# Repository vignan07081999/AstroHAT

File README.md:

### AstroHAT
## Raspberry Pi HAT for Astrophotography

This project is centered around developing a custom Raspberry Pi HAT designed to enhance astrophotography setups. It aims to streamline power management, integrate essential functionalities, and provide a platform for further expansion.

**Astrophotography**

Astrophotography is a specialized field of photography that captures celestial objects and phenomena. This often involves long exposure times, precise tracking, and specialized equipment.

**Stellarmate OS**

Stellarmate OS is a Linux distribution tailored for astrophotography. It provides a user-friendly interface and integrates with various astronomy software and hardware.

**ASCOM and INDI Protocols**

ASCOM and INDI are communication protocols widely used in astrophotography to facilitate interaction between different devices and software. ASCOM is primarily used on Windows, while INDI is platform-independent.

**Project Overview**

This custom Raspberry Pi HAT is currently under development with the following features and goals:

* **Power Management:**  Provides a centralized power solution for the Raspberry Pi and connected astrophotography devices. 
* **EEPROM:**  Includes an EEPROM for storing configuration data and other persistent information.
* **Real-Time Clock (RTC):**  Features a built-in RTC to ensure accurate timekeeping, even without an internet connection.

**Future Plans**

The project roadmap includes:

* **GPS Integration:**  Adding GPS functionality to enable precise location and time tracking.
* **Reduced Footprint:**  Optimizing the design to minimize the HAT's size and weight.
* **External USB Support:**  Including support for connecting additional USB devices.

**Current Status**

The project is actively in progress. The core functionalities of power management, EEPROM, and RTC are being developed and tested.

**Contributions**

Contributions, suggestions, and feedback are welcome! Please feel free to open issues or submit pull requests. 

**License**

This project is not yet licensed

**Disclaimer**

This project is experimental and may undergo significant changes. Use at your own risk.

**Let's make astrophotography more accessible and enjoyable!**

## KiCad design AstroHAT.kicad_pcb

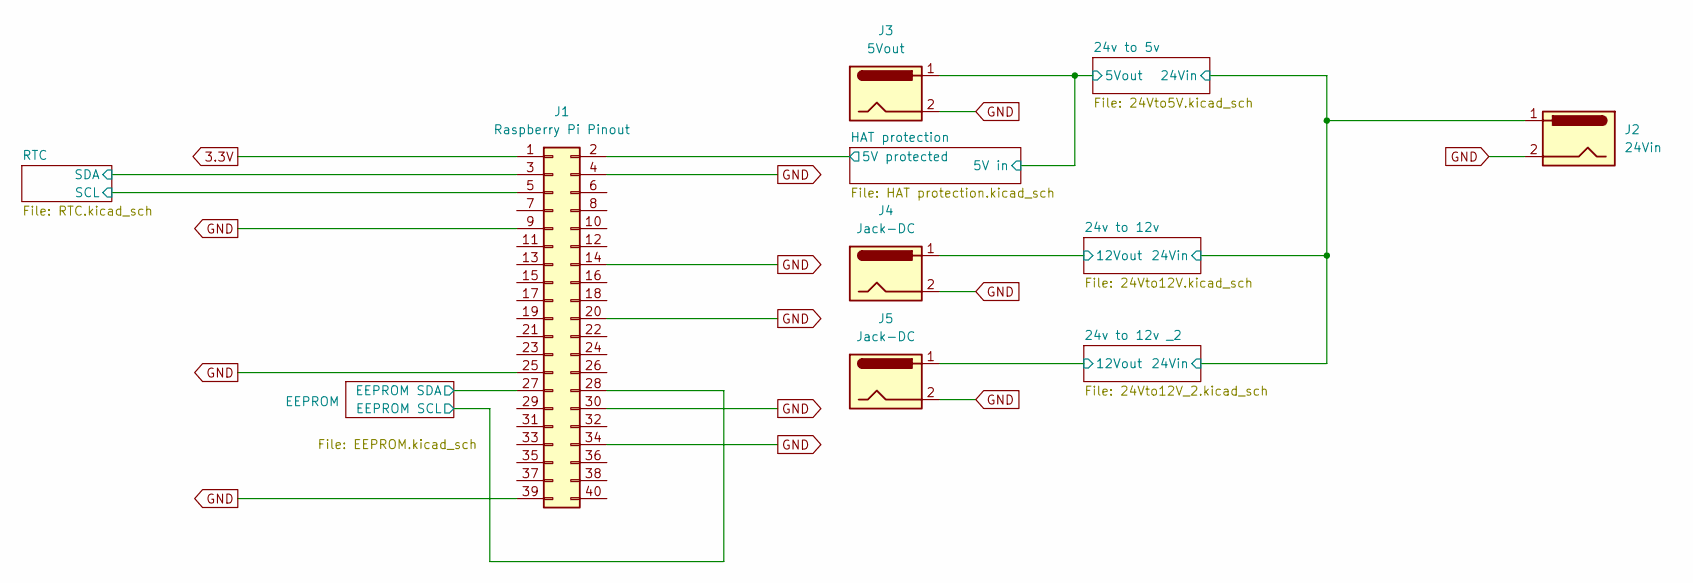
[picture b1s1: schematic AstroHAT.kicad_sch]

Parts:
J1: Raspberry Pi Pinout; PinSocket_2x20_P2.54mm_Vertical
J2: 24Vin; BarrelJack_CUI_PJ-102AH_Horizontal
J3: 5Vout; BarrelJack_CUI_PJ-102AH_Horizontal
J4, J5: Jack-DC; BarrelJack_CUI_PJ-102AH_Horizontal

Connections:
3.3V: J1.1; also elsewhere on the board
/24v to 5v/5Vout: J3.1; also elsewhere on the board
/24v to 12v _2/12Vout: J5.1; also elsewhere on the board
/24v to 12v _2/24Vin: J2.1; also elsewhere on the board
/24v to 12v/12Vout: J4.1; also elsewhere on the board
/EEPROM/EEPROM SCL: J1.28; also elsewhere on the board
/EEPROM/EEPROM SDA: J1.27; also elsewhere on the board
/HAT protection/5V protected: J1.2; also elsewhere on the board
/RTC/SCL: J1.5; also elsewhere on the board
/RTC/SDA: J1.3; also elsewhere on the board
GND: J1.4, J1.9, J1.14, J1.20, J1.25, J1.30, J1.34, J1.39, J2.2, J3.2, J4.2, J5.2; also elsewhere on the board

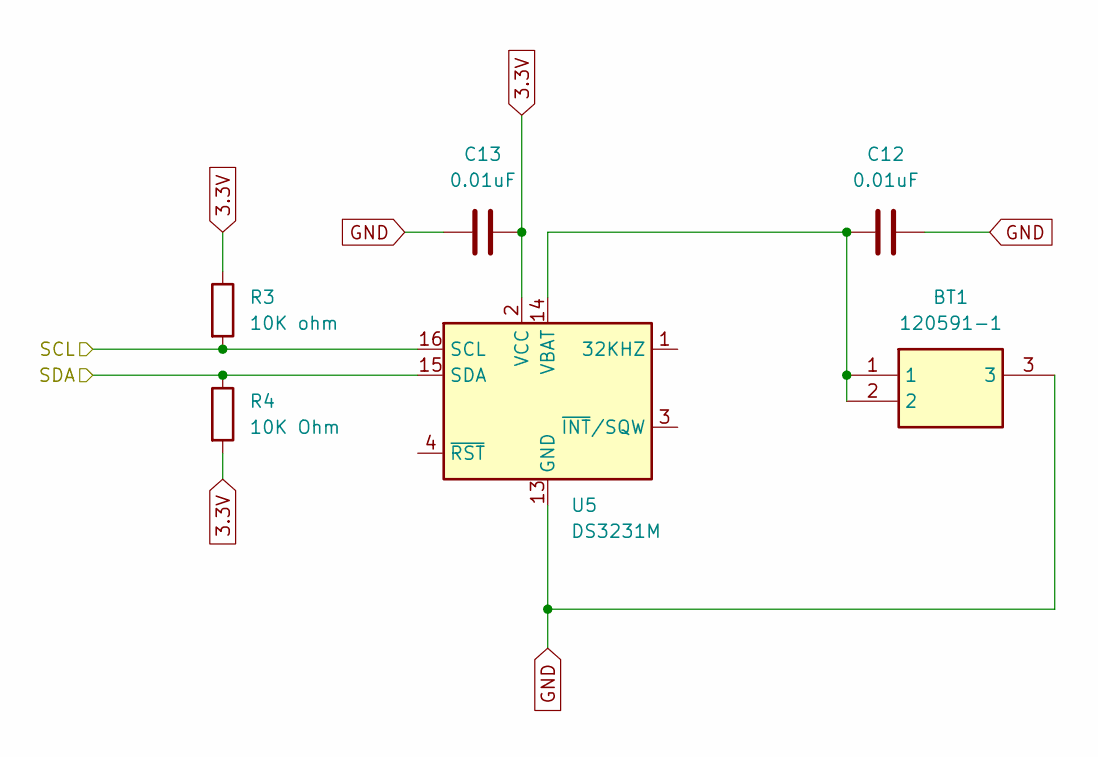
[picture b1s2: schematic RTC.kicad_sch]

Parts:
BT1: 120591-1; Mouser Part Number 571-1205911
C12, C13: 0.01uF; C_0201_0603Metric
R3: 10K ohm; R_2512_6332Metric
R4: 10K Ohm; R_2512_6332Metric
U5: DS3231M; SOIC-16W_7.5x10.3mm_P1.27mm

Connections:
3.3V: C13.2, R3.1, R4.2, U5.2 (VCC); also elsewhere on the board
/RTC/SCL: R3.2, U5.16 (SCL); also elsewhere on the board
/RTC/SDA: R4.1, U5.15 (SDA); also elsewhere on the board
GND: BT1.3, C12.2, C13.1, U5.5 (GND), U5.6 (GND), U5.7 (GND), U5.8 (GND), U5.9 (GND), U5.10 (GND), U5.11 (GND), U5.12 (GND), U5.13 (GND); also elsewhere on the board
unnamed: BT1.1, BT1.2, C12.1, U5.14 (VBAT)

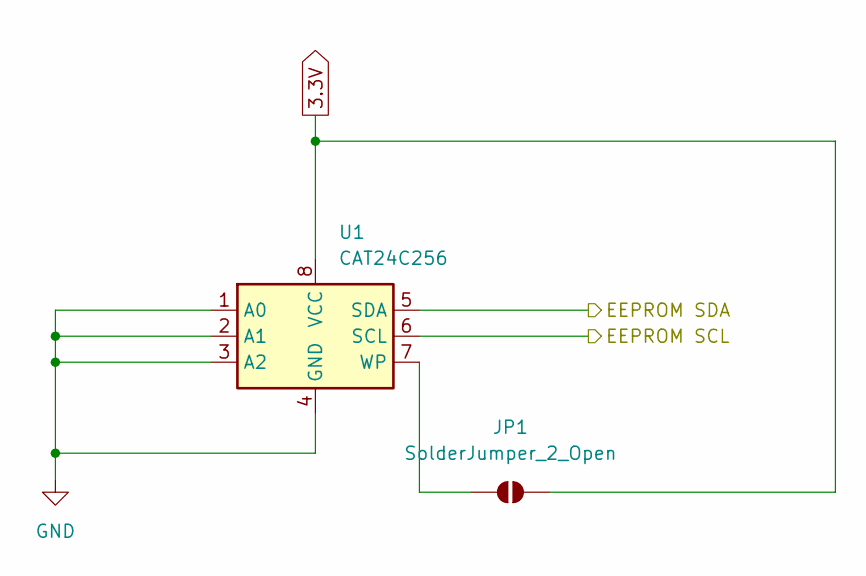
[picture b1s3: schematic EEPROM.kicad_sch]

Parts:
JP1: SolderJumper_2_Open; SolderJumper-2_P1.3mm_Open_RoundedPad1.0x1.5mm
U1: CAT24C256; SOIC127P600X175-8N

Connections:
3.3V: JP1.2 (B), U1.8 (VCC); also elsewhere on the board
/EEPROM/EEPROM SCL: U1.6 (SCL); also elsewhere on the board
/EEPROM/EEPROM SDA: U1.5 (SDA); also elsewhere on the board
GND: U1.1 (A0), U1.2 (A1), U1.3 (A2), U1.4 (GND); also elsewhere on the board
unnamed: JP1.1 (A), U1.7 (WP)

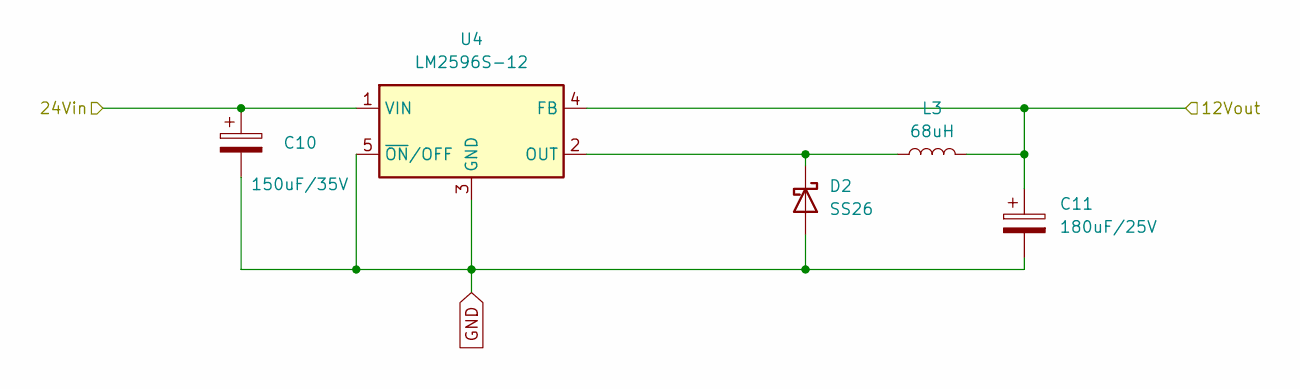
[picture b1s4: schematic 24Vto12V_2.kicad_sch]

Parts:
C10: 150uF/35V; EEHZA1H680P
C11: 180uF/25V; CAPAE830X700N
D2: SS26; D_SMA
L3: 68uH; PA4344683NLT
U4: LM2596S-12; TO-263-5_TabPin3

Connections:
/24v to 12v _2/12Vout: C11.1, L3.2, U4.4 (FB); also elsewhere on the board
/24v to 12v _2/24Vin: C10.1, U4.1 (VIN); also elsewhere on the board
GND: C10.2, C11.2, D2.2 (A), U4.3 (GND), U4.5 (~ON/OFF); also elsewhere on the board
unnamed: D2.1 (K), L3.1, U4.2 (OUT)

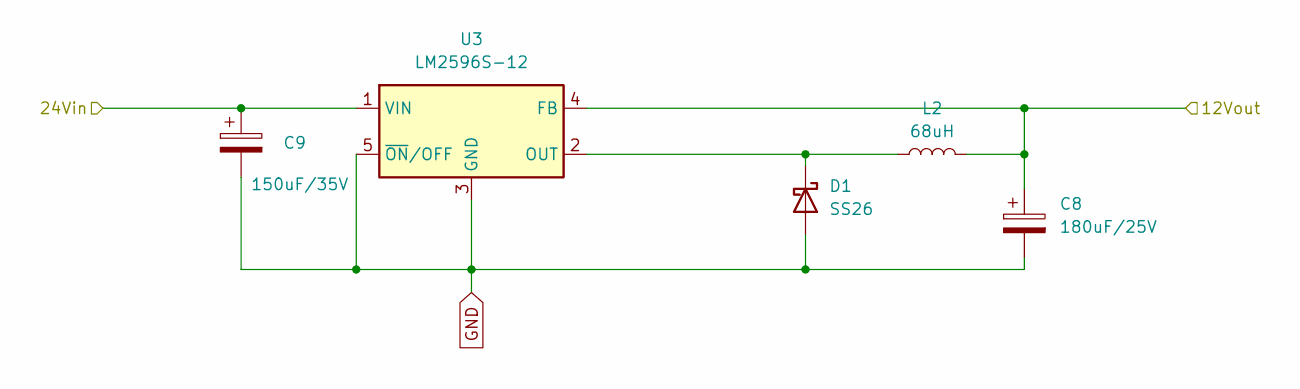
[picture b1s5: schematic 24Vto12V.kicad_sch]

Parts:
C8: 180uF/25V; CAPAE830X700N
C9: 150uF/35V; EEHZA1H680P
D1: SS26; D_SMA
L2: 68uH; PA4344683NLT
U3: LM2596S-12; TO-263-5_TabPin3

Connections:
/24v to 12v _2/24Vin: C9.1, U3.1 (VIN); also elsewhere on the board
/24v to 12v/12Vout: C8.1, L2.2, U3.4 (FB); also elsewhere on the board
GND: C8.2, C9.2, D1.2 (A), U3.3 (GND), U3.5 (~ON/OFF); also elsewhere on the board
unnamed: D1.1 (K), L2.1, U3.2 (OUT)

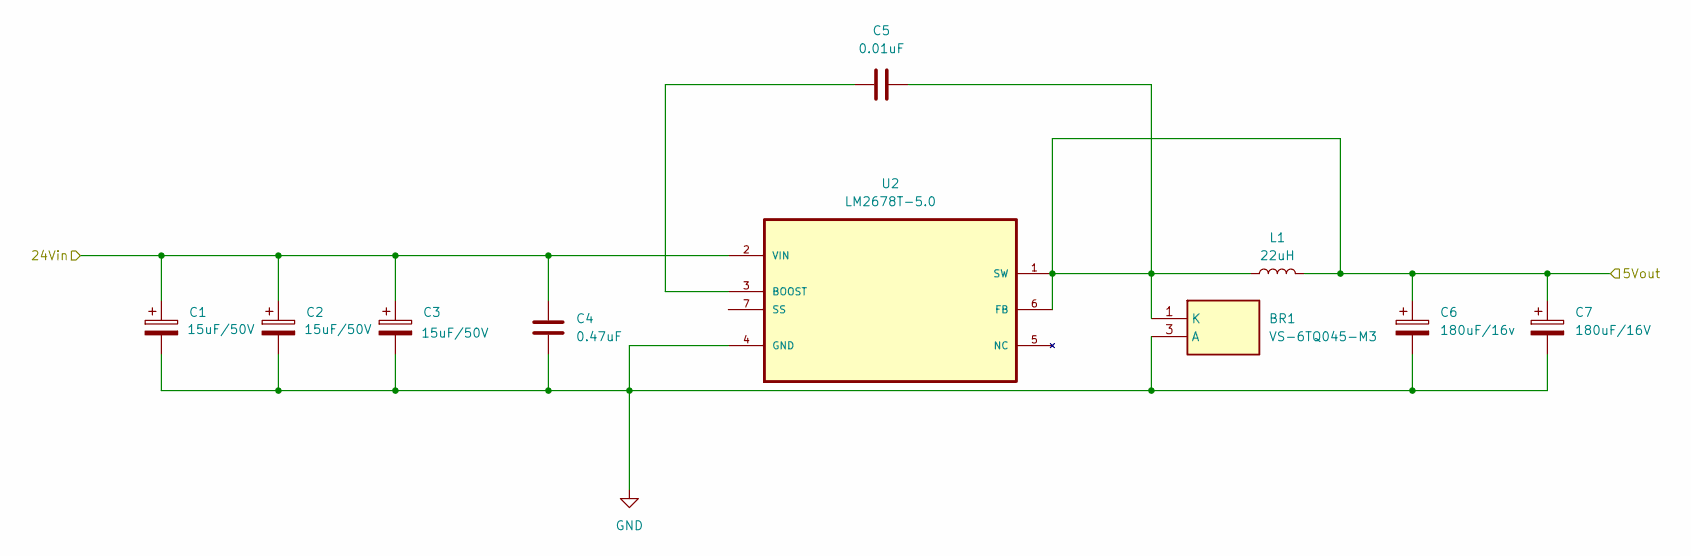
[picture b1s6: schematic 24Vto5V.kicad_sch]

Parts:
BR1: VS-6TQ045-M3; VS6TQ045STRLM3; Mouser Part Number 78-VS-6TQ045-M3
C1, C2, C3: 15uF/50V; CAPAE660X850N
C4: 0.47uF; CAPC3216X152N
C5: 0.01uF; C_0201_0603Metric
C6: 180uF/16v; CAPPC5958X380N
C7: 180uF/16V; CAPPC5958X380N
L1: 22uH; L_Wuerth_MAPI-4020
U2: LM2678T-5.0; TO127P1435X464-8N; MPN LLM2678T-5.0

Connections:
/24v to 5v/5Vout: BR1.1 (K), C5.1, C6.1, C7.1, L1.1, L1.2, U2.1 (SW), U2.6 (FB); also elsewhere on the board
/24v to 12v _2/24Vin: C1.1, C2.1, C3.1, C4.1, U2.2 (VIN); also elsewhere on the board
GND: BR1.3 (A), C1.2, C2.2, C3.2, C4.2, C6.2, C7.2, U2.4 (GND); also elsewhere on the board
unnamed: C5.2, U2.3 (BOOST)

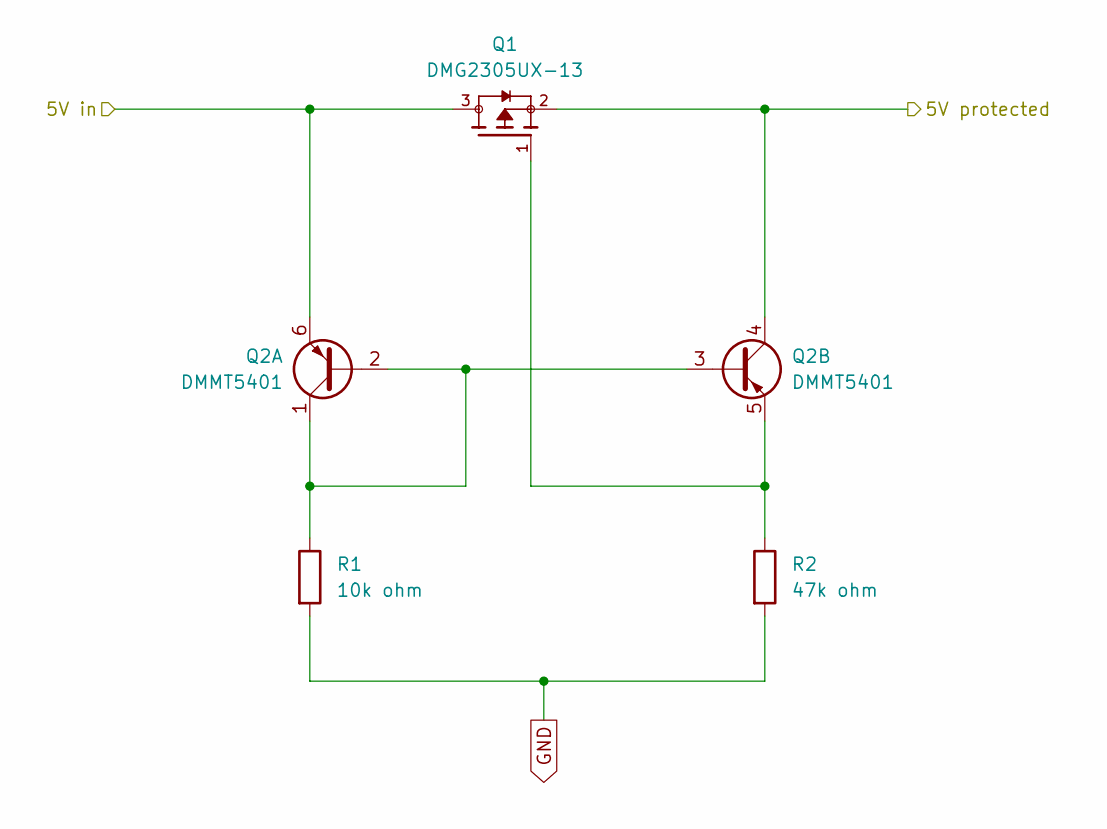
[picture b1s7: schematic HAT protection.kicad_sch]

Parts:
Q1: DMG2305UX-13; SOT91P240X110-3N; PARTREV 09/2018
Q2: DMMT5401; SOT-23-6
R1: 10k ohm; R_0201_0603Metric
R2: 47k ohm; R_0201_0603Metric

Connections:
/24v to 5v/5Vout: Q1.3, Q2.6 (E1); also elsewhere on the board
/HAT protection/5V protected: Q1.2, Q2.4 (C2); also elsewhere on the board
GND: R1.2, R2.2; also elsewhere on the board
unnamed: Q2.1 (C1), Q2.2 (B1), Q2.3 (B2), R1.1
unnamed: Q1.1, Q2.5 (E2), R2.1

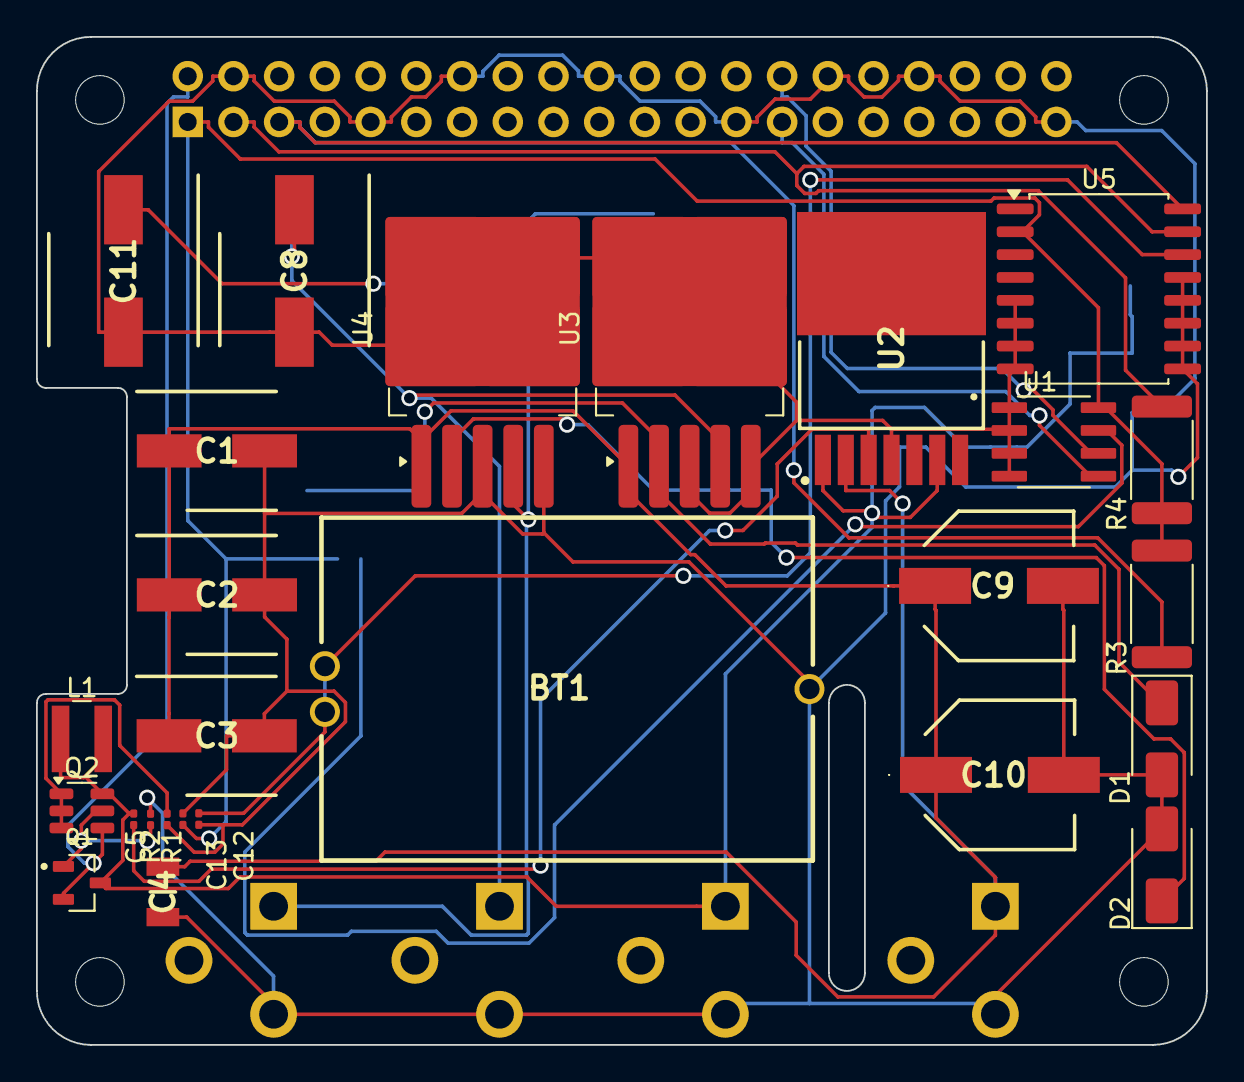
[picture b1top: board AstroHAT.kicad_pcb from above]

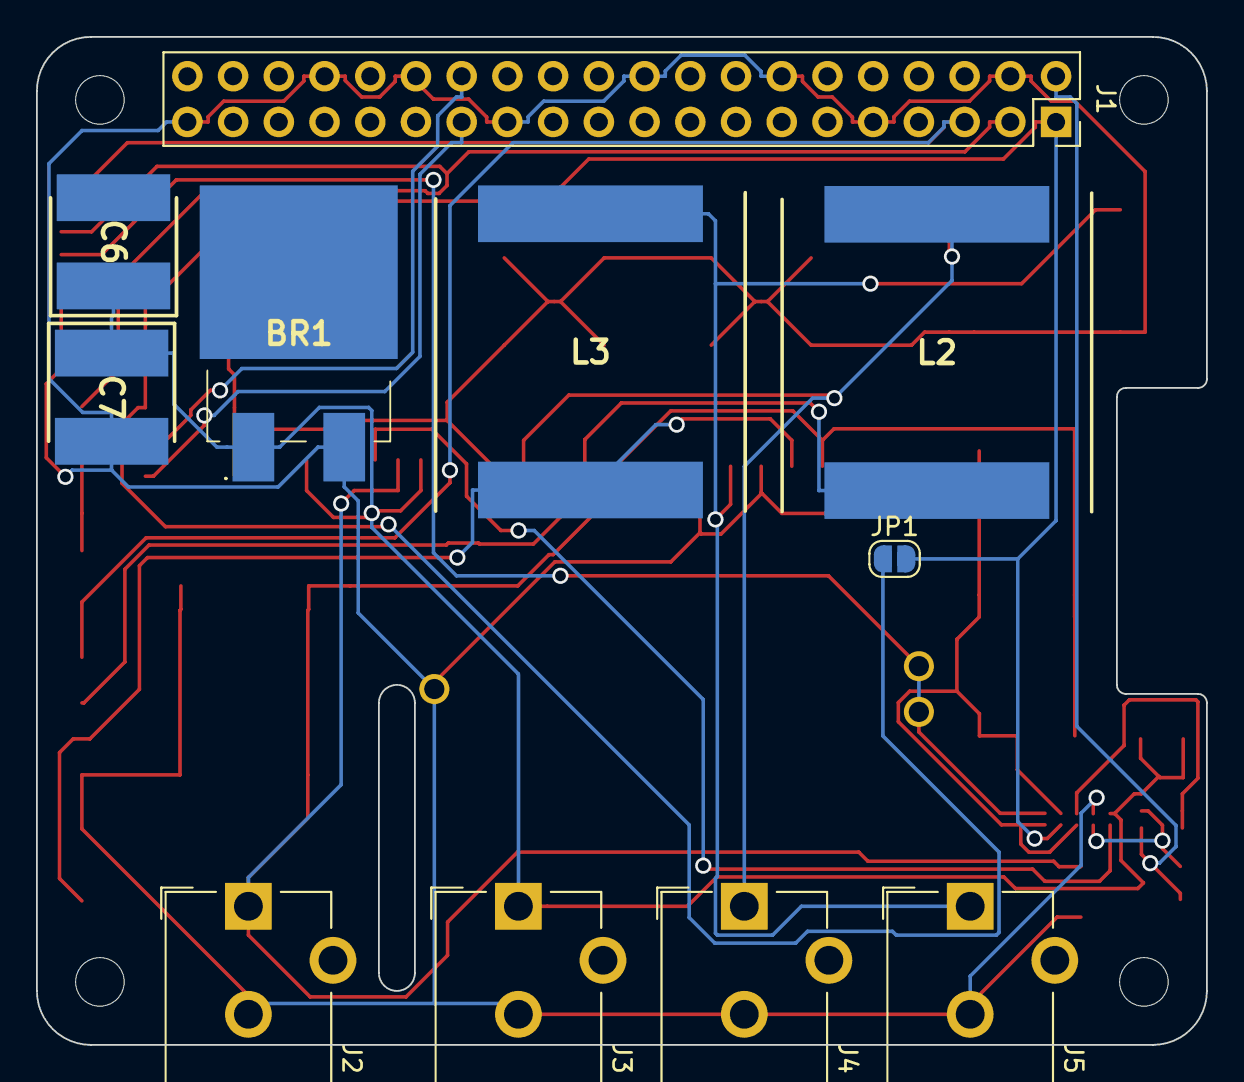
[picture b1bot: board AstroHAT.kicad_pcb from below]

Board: 2 copper layers, 65.0 x 56.0 mm, 41 parts (11 on the bottom side), 18 nets.

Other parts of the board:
MH1, MH2, MH3, MH4: MountingHole_2.7mm_M2.5
